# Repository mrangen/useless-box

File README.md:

## mrangen-fork
### KiCad Version
My friend was having trouble with the original files and asked if I could quickly remake it for them in KiCad. I'm not the original author of this design, I simply rebuilt the original author's design in KiCad.

# Smart Useless Box with ESP8266 and Gesture Sensor

A useless box made smarter with an ESP8266 microcontroller on a Wemos D1 Mini board and an APDS-9960 proximity sensor to give more funny responses.

## YAUB (Yet Another Useless Box)?

Useless machines are not new, there are many versions available. You can create a simple one using a lever switch, however that will react always the same way. Using a programmable microcontroller you can create **funny, unexpected responses**, and by adding a proximity sensor you can surprise the user with **actions before she would even turn on the switch**!

This is a programmable useless box, so you have the option to implement **additional reactions** when you want to to further improve this funny little toy. What's more the used controller board has WiFi connectivity, so you can **connect it to other online services** (e.g. IFTTT) or **smart assistants** (Alexa, Cortana etc.).

## Smart Useless Box in Action

Click the image below to see this box in action:

## Hardware

The following hardware components are required to build this project:

- 1 × [Wemos D1 Mini board](https://wiki.wemos.cc/products:d1:d1_mini)
- 1 × [APDS-9960 RGB, gesture and proximity sensor](https://www.sparkfun.com/products/12787) - there are multiple versions of this board, use one that follows the pinout of the SparkFun module to simplify wiring. I used [this](https://www.aliexpress.com/item/32768898229.html) cheap one from AliExpress.
- 2 × [SG90 servo motors](https://components101.com/servo-motor-basics-pinout-datasheet)
- 1 × Switch - you have to test this to ensure it flips easily and the servo is strong enough to flip it, so I bought mine in the nearest electronics hardware store.
- 1 × 1kΩ resistance
- Male pin headers:
  - 1 × 1x2 for the switch
  - 2 × 1x3 for the servo motors
  - 1 × 1x5 for the sensor
- Prototype board or PCB - to create a shield for the Wemos D1 Mini.
- Pin headers - to connect the shield to the Wemos D1 Mini.
- Dupont cables or wires with connectors.
- BluTack - to mount the wires and the controller board.
- M3 screws - to mount the lids.

## Wiring

The wiring is designed to create a custom shield for the Wemos D1 Mini ESP8266 microcontroller-based board, instead of soldering the cables directly to the board. In this way you can easily assemble the parts or even reuse them in the future.

### Schematics

### PCB

The PCB was designed with [Fritzing](https://fritzing.org), and you can [download the source file](./wiring/Useless-Box-Shield-v1.fzz) to further customize it to your needs.

You can also [download the Gerber files](./wiring/Useless-Box-Shield-v1-PCB-Gerber.zip) which you can use to order the PCB from your preferred PCB manufacturer. (Note: I've created my prototype manually then documented it in Fritzing, so I have not tested this PCB yet.)

## Software

The source code in this repo is created with [Visual Studio Code](https://code.visualstudio.com) using the [Arduino plugin from Microsoft](https://marketplace.visualstudio.com/items?itemName=vsciot-vscode.vscode-arduino), but it should work with the [Arduino IDE](https://www.arduino.cc/en/main/software) as well.

The code in this repository is preconfigured with the pin layout shown in the wiring diagram above, but if you decide to connect the parts to different pins, you have to update the values in the `config.h` file.

After finalizing the pin configuration (or using the default one) just upload the code to the Wemos D1 Mini board.

The responses of the box are implemented in the `useless-box.ino` file, and the `run()` function is responsible for selecting and executing the reaction to a flip of the switch or to a signal from the sensor. Feel free to add new logic or remove any existing reaction you don't like in this function.

## The Box

I designed a custom box for this project which can be 3D printed or even further customized. You can download the model from [Thingiverse](https://www.thingiverse.com/thing:3856965) or [MyMiniFactory](https://www.myminifactory.com/object/3d-print-100944).

Happy Printing! :)

## About the author

This project is maintained by [György Balássy](https://linkedin.com/in/balassy).

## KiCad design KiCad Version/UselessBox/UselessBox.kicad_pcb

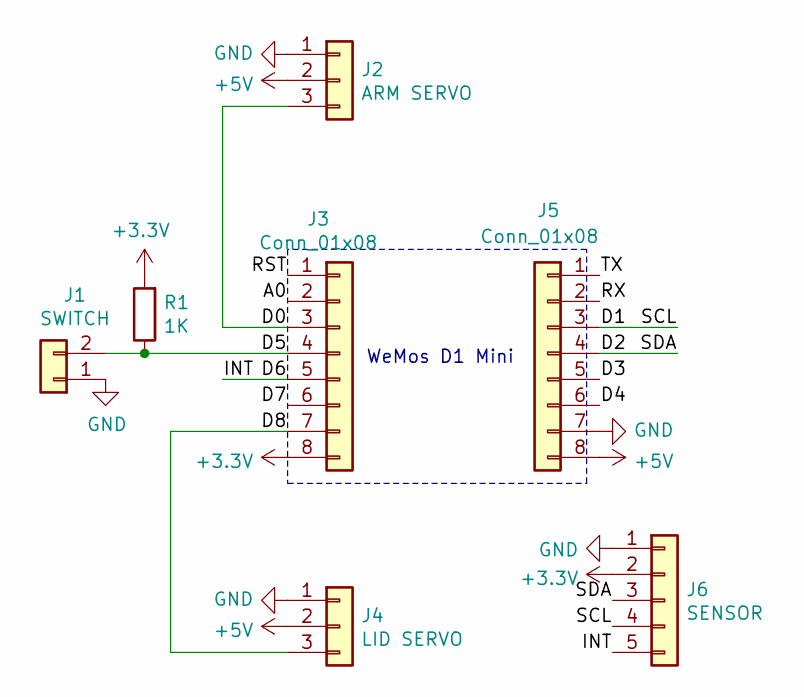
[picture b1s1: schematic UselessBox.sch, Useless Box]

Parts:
J1: SWITCH; PinSocket_1x02_P2.54mm_Vertical
J2: ARM SERVO; PinHeader_1x03_P2.54mm_Vertical
J3, J5: Conn_01x08; PinSocket_1x08_P2.54mm_Vertical
J4: LID SERVO; PinHeader_1x03_P2.54mm_Vertical
J6: SENSOR; PinSocket_1x05_P2.54mm_Vertical
R1: 1K; R_Axial_DIN0309_L9.0mm_D3.2mm_P12.70mm_Horizontal

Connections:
+3V3: J3.8, J6.2, R1.2
+5V: J2.2, J4.2, J5.8
/A0: J3.2
/D0: J2.3, J3.3
/D1: J5.3, J6.4
/D2: J5.4, J6.3
/D3: J5.5
/D4: J5.6
/D5: J1.2, J3.4, R1.1
/D6: J3.5, J6.5
/D7: J3.6
/D8: J3.7, J4.3
/RST: J3.1
/RX: J5.2
/TX: J5.1
GND: J1.1, J2.1, J4.1, J5.7, J6.1

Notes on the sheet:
WeMos D1 Mini

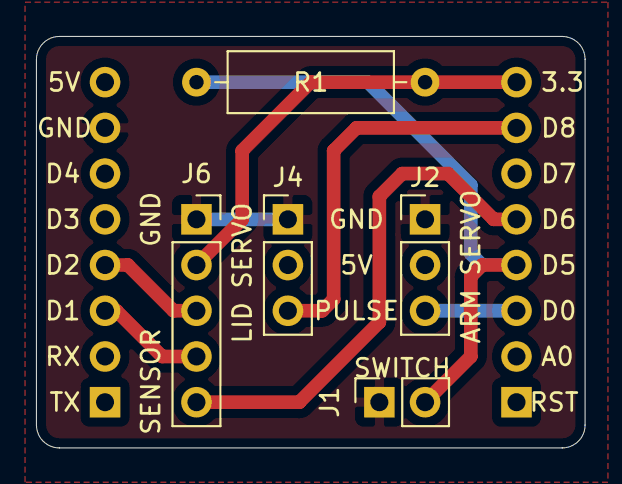
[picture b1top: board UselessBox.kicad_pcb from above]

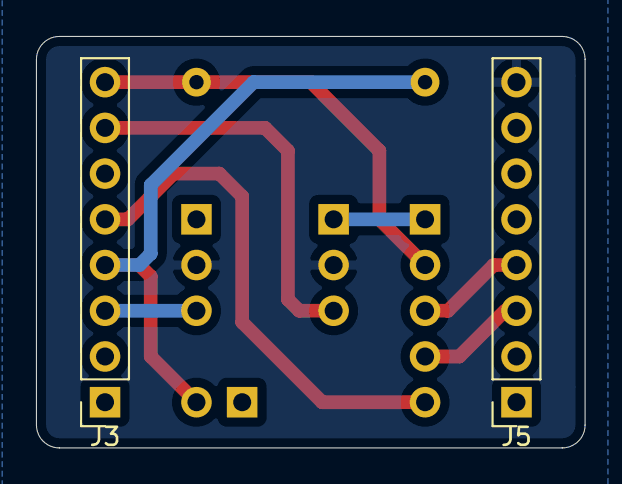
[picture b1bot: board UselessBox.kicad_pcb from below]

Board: 2 copper layers, 30.5 x 22.9 mm, 7 parts (2 on the bottom side), 9 nets.

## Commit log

2021-09-04 Made KiCad Version
    A friend was having trouble with the files in the original and asked if I could remake it in KiCad.
